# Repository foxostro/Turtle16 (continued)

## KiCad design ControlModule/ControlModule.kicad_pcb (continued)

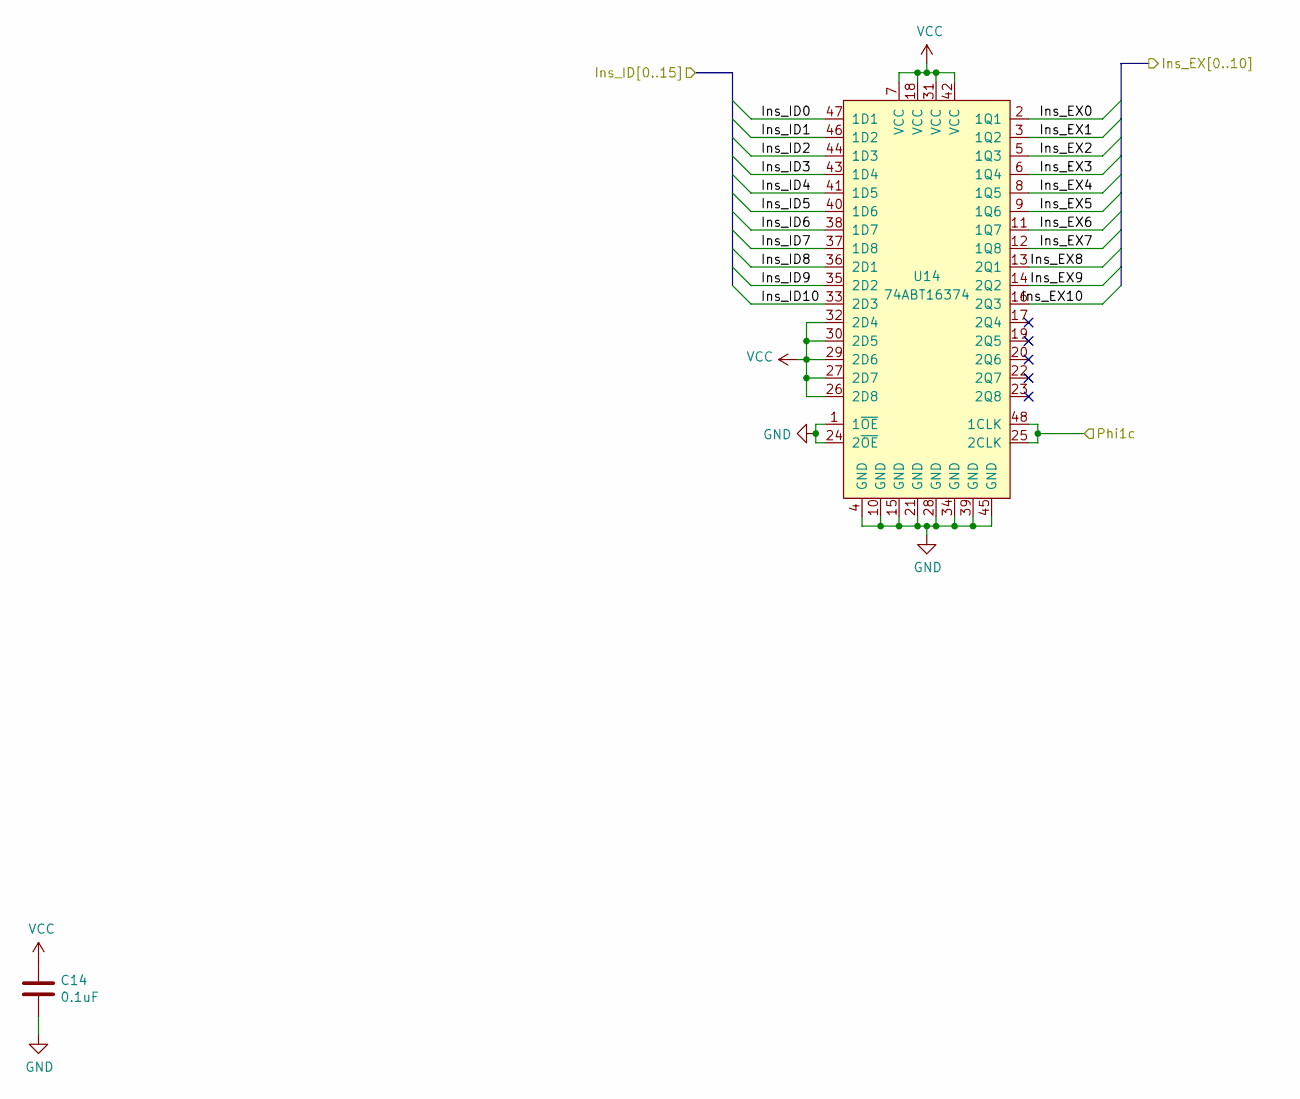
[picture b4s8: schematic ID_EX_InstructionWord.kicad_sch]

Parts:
C14: 0.1uF; C_0603_1608Metric_Pad1.08x0.95mm_HandSolder
U14: 74ABT16374; TSSOP-48_6.1x12.5mm_P0.5mm

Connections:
/ID Prototype Inputs/Ins_ID0: U14.47 (1D1); also elsewhere on the board
/ID Prototype Inputs/Ins_ID1: U14.46 (1D2); also elsewhere on the board
/ID Prototype Inputs/Ins_ID2: U14.44 (1D3); also elsewhere on the board
/ID Prototype Inputs/Ins_ID3: U14.43 (1D4); also elsewhere on the board
/ID Prototype Inputs/Ins_ID4: U14.41 (1D5); also elsewhere on the board
/ID Prototype Inputs/Ins_ID5: U14.40 (1D6); also elsewhere on the board
/ID Prototype Inputs/Ins_ID6: U14.38 (1D7); also elsewhere on the board
/ID Prototype Inputs/Ins_ID7: U14.37 (1D8); also elsewhere on the board
/ID Prototype Inputs/Ins_ID8: U14.36 (2D1); also elsewhere on the board
/ID Prototype Inputs/Ins_ID9: U14.35 (2D2); also elsewhere on the board
/ID Prototype Inputs/Ins_ID10: U14.33 (2D3); also elsewhere on the board
/ID Prototype Inputs/Phi1c: U14.25 (2CLK), U14.48 (1CLK); also elsewhere on the board
/ID Prototype Outputs/Ins_EX0: U14.2 (1Q1); also elsewhere on the board
/ID Prototype Outputs/Ins_EX1: U14.3 (1Q2); also elsewhere on the board
/ID Prototype Outputs/Ins_EX2: U14.5 (1Q3); also elsewhere on the board
/ID Prototype Outputs/Ins_EX3: U14.6 (1Q4); also elsewhere on the board
/ID Prototype Outputs/Ins_EX4: U14.8 (1Q5); also elsewhere on the board
/ID Prototype Outputs/Ins_EX5: U14.9 (1Q6); also elsewhere on the board
/ID Prototype Outputs/Ins_EX6: U14.11 (1Q7); also elsewhere on the board
/ID Prototype Outputs/Ins_EX7: U14.12 (1Q8); also elsewhere on the board
/ID Prototype Outputs/Ins_EX8: U14.13 (2Q1); also elsewhere on the board
/ID Prototype Outputs/Ins_EX9: U14.14 (2Q2); also elsewhere on the board
/ID Prototype Outputs/Ins_EX10: U14.16 (2Q3); also elsewhere on the board
GND: C14.2, U14.1 (1~OE), U14.4 (GND), U14.10 (GND), U14.15 (GND), U14.21 (GND), U14.24 (2~OE), U14.28 (GND), U14.34 (GND), U14.39 (GND), U14.45 (GND); also elsewhere on the board
VCC: C14.1, U14.7 (VCC), U14.18 (VCC), U14.26 (2D8), U14.27 (2D7), U14.29 (2D6), U14.30 (2D5), U14.31 (VCC), U14.32 (2D4), U14.42 (VCC); also elsewhere on the board

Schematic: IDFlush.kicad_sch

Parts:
C2, C3, C4, C17: 0.1uF; C_0603_1608Metric_Pad1.08x0.95mm_HandSolder
U1, U18: 74HC245; TSSOP-20_4.4x6.5mm_P0.65mm
U2, U17: 74AHCT16245; TSSOP-48_6.1x12.5mm_P0.5mm

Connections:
/ID/Ctl_Mid0: U17.47 (1A1); also elsewhere on the board
/ID/Ctl_Mid1: U17.46 (1A2); also elsewhere on the board
/ID/Ctl_Mid2: U17.44 (1A3); also elsewhere on the board
/ID/Ctl_Mid3: U17.43 (1A4); also elsewhere on the board
/ID/Ctl_Mid4: U17.41 (1A5); also elsewhere on the board
/ID/Ctl_Mid5: U17.40 (1A6); also elsewhere on the board
/ID/Ctl_Mid6: U17.38 (1A7); also elsewhere on the board
/ID/Ctl_Mid7: U17.37 (1A8); also elsewhere on the board
/ID/Ctl_Mid8: U17.36 (2A1); also elsewhere on the board
/ID/Ctl_Mid9: U17.35 (2A2); also elsewhere on the board
/ID/Ctl_Mid10: U17.33 (2A3); also elsewhere on the board
/ID/Ctl_Mid11: U17.32 (2A4); also elsewhere on the board
/ID/Ctl_Mid12: U17.30 (2A5); also elsewhere on the board
/ID/Ctl_Mid13: U17.29 (2A6); also elsewhere on the board
/ID/Ctl_Mid14: U17.27 (2A7); also elsewhere on the board
/ID/Ctl_Mid15: U17.26 (2A8); also elsewhere on the board
/ID/Ctl_Mid16: U18.11 (B7); also elsewhere on the board
/ID/Ctl_Mid17: U18.12 (B6); also elsewhere on the board
/ID/Ctl_Mid18: U18.13 (B5); also elsewhere on the board
/ID/Ctl_Mid19: U18.14 (B4); also elsewhere on the board
/ID/Ctl_Mid20: U18.15 (B3); also elsewhere on the board
/ID/Ctl_Mid21: U18.16 (B2); also elsewhere on the board
/ID/Ctl_Mid22: U18.17 (B1); also elsewhere on the board
/ID/Ctl_Mid23: U18.18 (B0); also elsewhere on the board
/ID/Hazard Control/FLUSH: U17.25 (2~OE), U17.48 (1~OE), U18.19 (CE); also elsewhere on the board
/ID/Hazard Control/~FLUSH: U1.19 (CE), U2.25 (2~OE), U2.48 (1~OE); also elsewhere on the board
/ID/ID Flush/Ctl_ID0: U2.47 (1A1), U17.2 (1B1); also elsewhere on the board
/ID/ID Flush/Ctl_ID1: U2.46 (1A2), U17.3 (1B2); also elsewhere on the board
/ID/ID Flush/Ctl_ID2: U2.44 (1A3), U17.5 (1B3); also elsewhere on the board
/ID/ID Flush/Ctl_ID3: U2.43 (1A4), U17.6 (1B4); also elsewhere on the board
/ID/ID Flush/Ctl_ID4: U2.41 (1A5), U17.8 (1B5); also elsewhere on the board
/ID/ID Flush/Ctl_ID5: U2.40 (1A6), U17.9 (1B6); also elsewhere on the board
/ID/ID Flush/Ctl_ID6: U2.38 (1A7), U17.11 (1B7); also elsewhere on the board
/ID/ID Flush/Ctl_ID7: U2.37 (1A8), U17.12 (1B8); also elsewhere on the board
/ID/ID Flush/Ctl_ID8: U2.36 (2A1), U17.13 (2B1); also elsewhere on the board
/ID/ID Flush/Ctl_ID9: U2.35 (2A2), U17.14 (2B2); also elsewhere on the board
/ID/ID Flush/Ctl_ID10: U2.33 (2A3), U17.16 (2B3); also elsewhere on the board
/ID/ID Flush/Ctl_ID11: U2.32 (2A4), U17.17 (2B4); also elsewhere on the board
/ID/ID Flush/Ctl_ID12: U2.30 (2A5), U17.19 (2B5); also elsewhere on the board
/ID/ID Flush/Ctl_ID13: U2.29 (2A6), U17.20 (2B6); also elsewhere on the board
/ID/ID Flush/Ctl_ID14: U2.27 (2A7), U17.22 (2B7); also elsewhere on the board
/ID/ID Flush/Ctl_ID15: U2.26 (2A8), U17.23 (2B8); also elsewhere on the board
/ID/ID Flush/Ctl_ID16: U1.11 (B7), U18.9 (A7); also elsewhere on the board
/ID/ID Flush/Ctl_ID17: U1.12 (B6), U18.8 (A6); also elsewhere on the board
/ID/ID Flush/Ctl_ID18: U1.13 (B5), U18.7 (A5); also elsewhere on the board
/ID/ID Flush/Ctl_ID19: U1.14 (B4), U18.6 (A4); also elsewhere on the board
/ID/ID Flush/Ctl_ID20: U1.15 (B3), U18.5 (A3); also elsewhere on the board
/ID/ID Flush/Ctl_ID21: U1.16 (B2), U18.4 (A2); also elsewhere on the board
/ID/ID Flush/Ctl_ID22: U1.17 (B1), U18.3 (A1); also elsewhere on the board
/ID/ID Flush/Ctl_ID23: U1.18 (B0), U18.2 (A0); also elsewhere on the board
GND: C2.2, C3.2, C4.2, C17.2, U1.10 (GND), U2.1 (1DIR), U2.4 (GND), U2.10 (GND), U2.15 (GND), U2.21 (GND), U2.24 (2DIR), U2.28 (GND), U2.34 (GND), U2.39 (GND), U2.45 (GND), U17.4 (GND), U17.10 (GND), U17.15 (GND), U17.21 (GND), U17.28 (GND), U17.34 (GND), U17.39 (GND), U17.45 (GND), U18.1 (A->B), U18.10 (GND); also elsewhere on the board
VCC: C2.1, C3.1, C4.1, C17.1, U1.1 (A->B), U1.2 (A0), U1.3 (A1), U1.4 (A2), U1.5 (A3), U1.6 (A4), U1.7 (A5), U1.8 (A6), U1.9 (A7), U1.20 (VCC), U2.2 (1B1), U2.3 (1B2), U2.5 (1B3), U2.6 (1B4), U2.7 (VCC), U2.8 (1B5), U2.9 (1B6), U2.11 (1B7), U2.12 (1B8), U2.13 (2B1), U2.14 (2B2), U2.16 (2B3), U2.17 (2B4), U2.18 (VCC), U2.19 (2B5), U2.20 (2B6), U2.22 (2B7), U2.23 (2B8), U2.31 (VCC), U2.42 (VCC), U17.1 (1DIR), U17.7 (VCC), U17.18 (VCC), U17.24 (2DIR), U17.31 (VCC), U17.42 (VCC), U18.20 (VCC); also elsewhere on the board

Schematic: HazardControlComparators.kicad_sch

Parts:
C10, C11, C12, C13: 0.1uF; C_0603_1608Metric_Pad1.08x0.95mm_HandSolder
TP34: SEL_B_MATCHES_SEL_C_MEM; TestPoint_Pad_D1.0mm
TP35: SEL_A_MATCHES_SEL_C_MEM; TestPoint_Pad_D1.0mm
TP36: SEL_A_MATCHES_SEL_C_EX; TestPoint_Pad_D1.0mm
TP37: SEL_B_MATCHES_SEL_C_EX; TestPoint_Pad_D1.0mm
U10, U11, U12, U13: 74F521; SOIC-20W_7.5x12.8mm_P1.27mm

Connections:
/ID Prototype Inputs/Ins_ID2: U11.2 (P0), U12.2 (P0); also elsewhere on the board
/ID Prototype Inputs/Ins_ID3: U11.4 (P1), U12.4 (P1); also elsewhere on the board
/ID Prototype Inputs/Ins_ID4: U11.6 (P2), U12.6 (P2); also elsewhere on the board
/ID Prototype Inputs/Ins_ID5: U10.2 (P0), U13.2 (P0); also elsewhere on the board
/ID Prototype Inputs/Ins_ID6: U10.4 (P1), U13.4 (P1); also elsewhere on the board
/ID Prototype Inputs/Ins_ID7: U10.6 (P2), U13.6 (P2); also elsewhere on the board
/ID Prototype Inputs/SelC_MEM0: U12.3 (Q0), U13.3 (Q0); also elsewhere on the board
/ID Prototype Inputs/SelC_MEM1: U12.5 (Q1), U13.5 (Q1); also elsewhere on the board
/ID Prototype Inputs/SelC_MEM2: U12.7 (Q2), U13.7 (Q2); also elsewhere on the board
/ID Prototype Outputs/Ins_EX8: U10.3 (Q0), U11.3 (Q0); also elsewhere on the board
/ID Prototype Outputs/Ins_EX9: U10.5 (Q1), U11.5 (Q1); also elsewhere on the board
/ID Prototype Outputs/Ins_EX10: U10.7 (Q2), U11.7 (Q2); also elsewhere on the board
/ID/Hazard Control/Hazard Control Comparators/SEL_A_MATCHES_SEL_C_EX: TP36.1, U10.19 (~P=Q); also elsewhere on the board
/ID/Hazard Control/Hazard Control Comparators/SEL_A_MATCHES_SEL_C_MEM: TP35.1, U13.19 (~P=Q); also elsewhere on the board
/ID/Hazard Control/Hazard Control Comparators/SEL_B_MATCHES_SEL_C_EX: TP37.1, U11.19 (~P=Q); also elsewhere on the board
/ID/Hazard Control/Hazard Control Comparators/SEL_B_MATCHES_SEL_C_MEM: TP34.1, U12.19 (~P=Q); also elsewhere on the board
GND: C10.2, C11.2, C12.2, C13.2, U10.1 (~OE), U10.8 (P3), U10.9 (Q3), U10.10 (GND), U10.11 (P4), U10.12 (Q4), U10.13 (P5), U10.14 (Q5), U10.15 (P6), U10.16 (Q6), U10.17 (P7), U10.18 (Q7), U11.1 (~OE), U11.8 (P3), U11.9 (Q3), U11.10 (GND), U11.11 (P4), U11.12 (Q4), U11.13 (P5), U11.14 (Q5), U11.15 (P6), U11.16 (Q6), U11.17 (P7), U11.18 (Q7), U12.1 (~OE), U12.8 (P3), U12.9 (Q3), U12.10 (GND), U12.11 (P4), U12.12 (Q4), U12.13 (P5), U12.14 (Q5), U12.15 (P6), U12.16 (Q6), U12.17 (P7), U12.18 (Q7), U13.1 (~OE), U13.8 (P3), U13.9 (Q3), U13.10 (GND), U13.11 (P4), U13.12 (Q4), U13.13 (P5), U13.14 (Q5), U13.15 (P6), U13.16 (Q6), U13.17 (P7), U13.18 (Q7); also elsewhere on the board
VCC: C10.1, C11.1, C12.1, C13.1, U10.20 (VCC), U11.20 (VCC), U12.20 (VCC), U13.20 (VCC); also elsewhere on the board

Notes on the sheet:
SelA0
SelB1
SelA2
SelA1
SelB2
SelB0

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
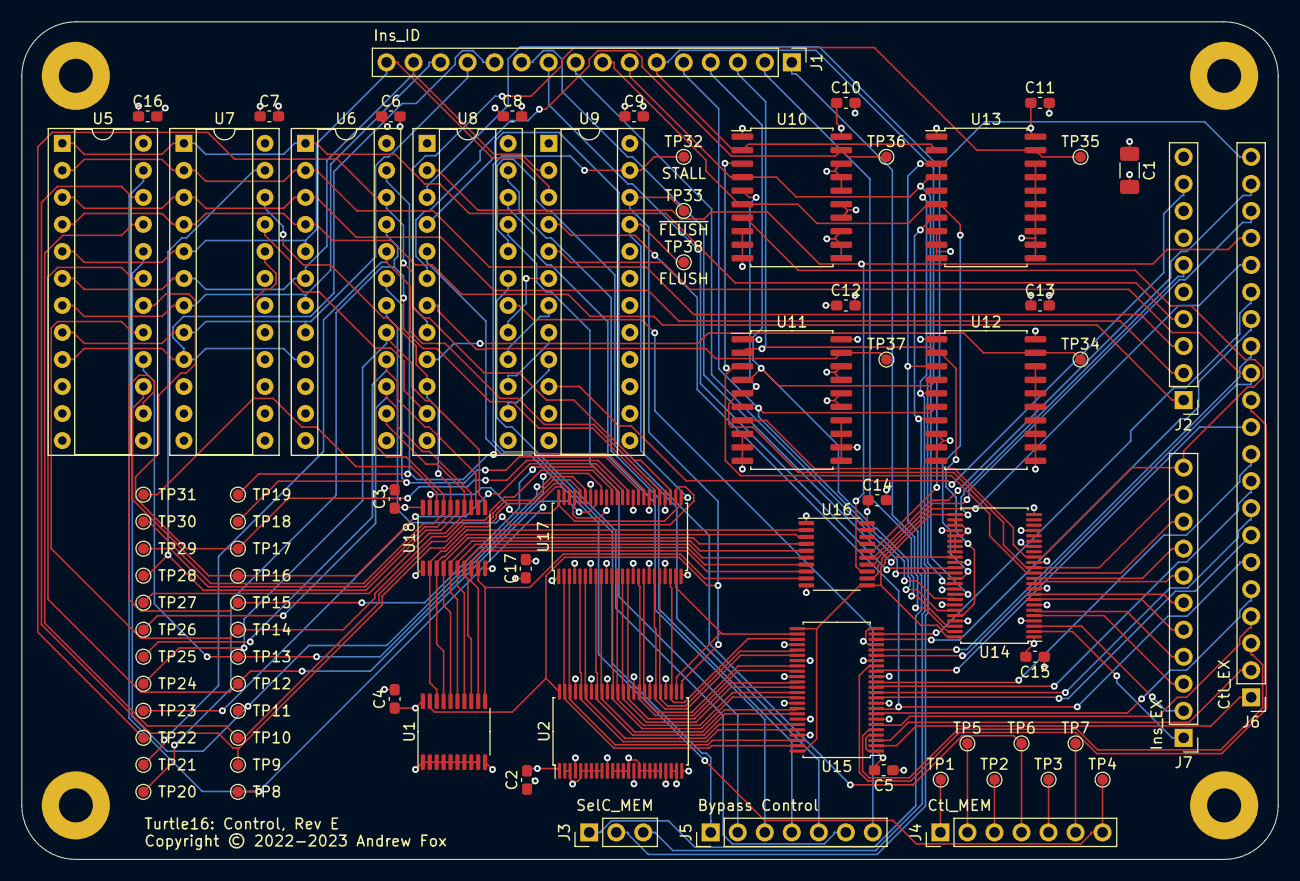
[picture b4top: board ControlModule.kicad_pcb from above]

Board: 4 copper layers, 118.1 x 78.7 mm, 82 parts (0 on the bottom side), 131 nets.

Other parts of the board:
TP2: Ctl_MEM16; TestPoint_Pad_D1.0mm
TP3: Ctl_Mid0; TestPoint_Pad_D1.0mm
TP4: Ctl_MEM20; TestPoint_Pad_D1.0mm
TP5: Ctl_MEM15; TestPoint_Pad_D1.0mm
TP6: Ctl_MEM17; TestPoint_Pad_D1.0mm
TP7: Ctl_MEM19; TestPoint_Pad_D1.0mm

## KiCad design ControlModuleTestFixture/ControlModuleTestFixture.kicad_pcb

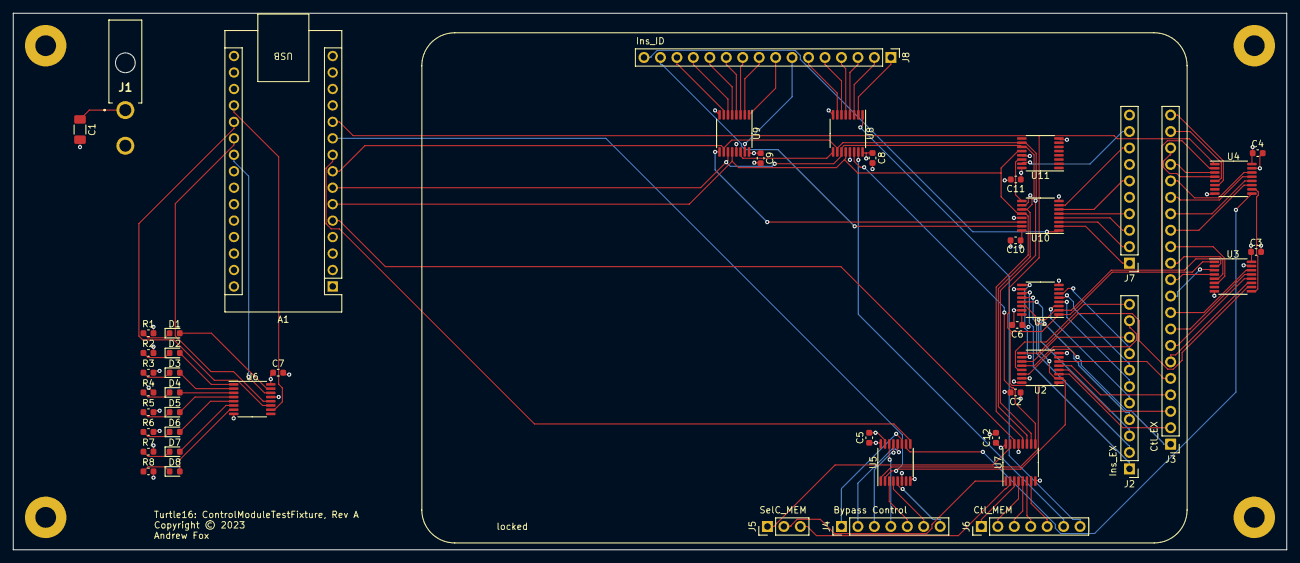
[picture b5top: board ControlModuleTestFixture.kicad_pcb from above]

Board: 4 copper layers, 196.5 x 82.8 mm, 52 parts (0 on the bottom side), 109 nets.

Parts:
A1: Arduino_Nano_Every; Arduino_Nano
C1: 100µF; C_1206_3216Metric_Pad1.33x1.80mm_HandSolder
C2, C3, C4, C5, C6, C7, C8, C9, C10, C11, C12: 0.1µF; C_0603_1608Metric
D1, D2, D3, D4, D5, D6, D7, D8: Red; LED_0603_1608Metric
H1, H2, H3, H4: MountingHole_Pad; MountingHole_3.2mm_M3_Pad
J1: Power; 172448-0002
J2: Ins_EX; PinHeader_1x11_P2.54mm_Vertical
J3: Ctl_EX; PinHeader_1x21_P2.54mm_Vertical
J4: Bypass Control; PinHeader_1x07_P2.54mm_Vertical
J5: SelC_MEM; PinHeader_1x03_P2.54mm_Vertical
J6: Ctl_MEM; PinHeader_1x07_P2.54mm_Vertical
J7: Control Signals; PinHeader_1x10_P2.54mm_Vertical
J8: Ins_ID; PinHeader_1x16_P2.54mm_Vertical
R1, R2, R3, R4, R5, R6, R7, R8: 270R; C_0603_1608Metric
U1, U2, U3, U4, U5: 74HC165; TSSOP-16_4.4x5mm_P0.65mm
U6, U7, U8, U9, U10, U11: 74HC595; TSSOP-16_4.4x5mm_P0.65mm

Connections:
/ID Prototype Inputs/Carry: J7.1, U10.2 (QC)
/ID Prototype Inputs/Ctl_MEM14: J6.1, U7.3 (QD)
/ID Prototype Inputs/Ctl_MEM15: J6.2, U7.4 (QE)
/ID Prototype Inputs/Ctl_MEM16: J6.3, U7.5 (QF)
/ID Prototype Inputs/Ctl_MEM17: J6.4, U7.6 (QG)
/ID Prototype Inputs/Ctl_MEM18: J6.5, U7.7 (QH)
/ID Prototype Inputs/Ctl_MEM19: J6.6, U8.15 (QA)
/ID Prototype Inputs/Ctl_MEM20: J6.7, U8.1 (QB)
/ID Prototype Inputs/Ins_ID0: J8.1, U8.2 (QC)
/ID Prototype Inputs/Ins_ID1: J8.2, U8.3 (QD)
/ID Prototype Inputs/Ins_ID2: J8.3, U8.4 (QE)
/ID Prototype Inputs/Ins_ID3: J8.4, U8.5 (QF)
/ID Prototype Inputs/Ins_ID4: J8.5, U8.6 (QG)
/ID Prototype Inputs/Ins_ID5: J8.6, U8.7 (QH)
/ID Prototype Inputs/Ins_ID6: J8.7, U9.15 (QA)
/ID Prototype Inputs/Ins_ID7: J8.8, U9.1 (QB)
/ID Prototype Inputs/Ins_ID8: J8.9, U9.2 (QC)
/ID Prototype Inputs/Ins_ID9: J8.10, U9.3 (QD)
/ID Prototype Inputs/Ins_ID10: J8.11, U9.4 (QE)
/ID Prototype Inputs/Ins_ID11: J8.12, U9.5 (QF)
/ID Prototype Inputs/Ins_ID12: J8.13, U9.6 (QG)
/ID Prototype Inputs/Ins_ID13: J8.14, U9.7 (QH)
/ID Prototype Inputs/Ins_ID14: J8.15, U10.15 (QA)
/ID Prototype Inputs/Ins_ID15: J8.16, U10.1 (QB)
/ID Prototype Inputs/N: J7.4, U10.5 (QF)
/ID Prototype Inputs/OVF: J7.3, U10.4 (QE)
/ID Prototype Inputs/Phi1c: J7.6, U10.6 (QG)
/ID Prototype Inputs/Phi2: J7.8, U10.7 (QH)
/ID Prototype Inputs/SelC_MEM0: J5.1, U7.15 (QA)
/ID Prototype Inputs/SelC_MEM1: J5.2, U7.1 (QB)
/ID Prototype Inputs/SelC_MEM2: J5.3, U7.2 (QC)
/ID Prototype Inputs/Z: J7.2, U10.3 (QD)
/ID Prototype Inputs/~RST_sync: J7.9, U11.15 (QA)
/ID Prototype Outputs/Ctl_EX0: J3.1, U2.14 (D3)
/ID Prototype Outputs/Ctl_EX1: J3.2, U2.3 (D4)
/ID Prototype Outputs/Ctl_EX2: J3.3, U2.4 (D5)
/ID Prototype Outputs/Ctl_EX3: J3.4, U2.5 (D6)
/ID Prototype Outputs/Ctl_EX4: J3.5, U2.6 (D7)
/ID Prototype Outputs/Ctl_EX5: J3.6, U3.11 (D0)
/ID Prototype Outputs/Ctl_EX6: J3.7, U3.12 (D1)
/ID Prototype Outputs/Ctl_EX7: J3.8, U3.13 (D2)
/ID Prototype Outputs/Ctl_EX8: J3.9, U3.14 (D3)
/ID Prototype Outputs/Ctl_EX9: J3.10, U3.3 (D4)
/ID Prototype Outputs/Ctl_EX10: J3.11, U3.4 (D5)
/ID Prototype Outputs/Ctl_EX11: J3.12, U3.5 (D6)
/ID Prototype Outputs/Ctl_EX12: J3.13, U3.6 (D7)
/ID Prototype Outputs/Ctl_EX13: J3.14, U4.11 (D0)
/ID Prototype Outputs/Ctl_EX14: J3.15, U4.12 (D1)
/ID Prototype Outputs/Ctl_EX15: J3.16, U4.13 (D2)
/ID Prototype Outputs/Ctl_EX16: J3.17, U4.14 (D3)
/ID Prototype Outputs/Ctl_EX17: J3.18, U4.3 (D4)
/ID Prototype Outputs/Ctl_EX18: J3.19, U4.4 (D5)
/ID Prototype Outputs/Ctl_EX19: J3.20, U4.5 (D6)
/ID Prototype Outputs/Ctl_EX20: J3.21, U4.6 (D7)
/ID Prototype Outputs/FWD_A: J4.2, U5.12 (D1)
/ID Prototype Outputs/FWD_B: J4.5, U5.3 (D4)
/ID Prototype Outputs/FWD_EX_TO_A: J4.3, U5.13 (D2)
/ID Prototype Outputs/FWD_EX_TO_B: J4.6, U5.4 (D5)
/ID Prototype Outputs/FWD_MEM_TO_A: J4.4, U5.14 (D3)
/ID Prototype Outputs/FWD_MEM_TO_B: J4.7, U5.5 (D6)
/ID Prototype Outputs/Ins_EX0: J2.1, U1.11 (D0)
/ID Prototype Outputs/Ins_EX1: J2.2, U1.12 (D1)
/ID Prototype Outputs/Ins_EX2: J2.3, U1.13 (D2)
/ID Prototype Outputs/Ins_EX3: J2.4, U1.14 (D3)
/ID Prototype Outputs/Ins_EX4: J2.5, U1.3 (D4)
/ID Prototype Outputs/Ins_EX5: J2.6, U1.4 (D5)
/ID Prototype Outputs/Ins_EX6: J2.7, U1.5 (D6)
/ID Prototype Outputs/Ins_EX7: J2.8, U1.6 (D7)
/ID Prototype Outputs/Ins_EX8: J2.9, U2.11 (D0)
/ID Prototype Outputs/Ins_EX9: J2.10, U2.12 (D1)
/ID Prototype Outputs/Ins_EX10: J2.11, U2.13 (D2)
/ID Prototype Outputs/STALL: J4.1, U5.11 (D0)
/LED Output/RCLK: A1.21 (A2), U6.12 (RCLK)
/LED Output/SCK: A1.20 (A1), U6.11 (SRCLK)
/LED Output/SI: A1.22 (A3), U6.14 (SER)
/LED Output/~CLR: A1.19 (A0), U6.10 (~SRCLR)
/Test Fixture Inputs/SCK: A1.10 (D7), U1.2 (CP), U2.2 (CP), U3.2 (CP), U4.2 (CP), U5.2 (CP)
/Test Fixture Inputs/SO: A1.9 (D6), U5.9 (Q7)
/Test Fixture Inputs/~PL: A1.11 (D8), U1.1 (~PL), U2.1 (~PL), U3.1 (~PL), U4.1 (~PL), U5.1 (~PL)
/Test Fixture Outputs/RCLK: A1.6 (D3), U7.12 (RCLK), U8.12 (RCLK), U9.12 (RCLK), U10.12 (RCLK), U11.12 (RCLK)
/Test Fixture Outputs/SCK: A1.7 (D4), U7.11 (SRCLK), U8.11 (SRCLK), U9.11 (SRCLK), U10.11 (SRCLK), U11.11 (SRCLK)
/Test Fixture Outputs/SI: A1.5 (D2), U7.14 (SER)
/Test Fixture Outputs/~CLR: A1.8 (D5), U7.10 (~SRCLR), U8.10 (~SRCLR), U9.10 (~SRCLR), U10.10 (~SRCLR), U11.10 (~SRCLR)
GND: A1.4 (GND), A1.29 (GND), C1.2, C2.2, C3.2, C4.2, C5.2, C6.2, C7.2, C8.2, C9.2, C10.2, C11.2, C12.2, H1.1, H2.1, H3.1, H4.1, J1.2, J7.5, J7.7, R1.2, R2.2, R3.2, R4.2, R5.2, R6.2, R7.2, R8.2, U1.8 (GND), U1.10 (DS), U1.15 (~CE), U2.8 (GND), U2.15 (~CE), U3.8 (GND), U3.15 (~CE), U4.8 (GND), U4.15 (~CE), U5.6 (D7), U5.8 (GND), U5.15 (~CE), U6.8 (GND), U6.13 (~OE), U7.8 (GND), U7.13 (~OE), U8.8 (GND), U8.13 (~OE), U9.8 (GND), U9.13 (~OE), U10.8 (GND), U10.13 (~OE), U11.8 (GND), U11.13 (~OE)
unnamed: D1.2 (A), U6.15 (QA)
unnamed: D1.1 (K), R1.1
unnamed: D2.2 (A), U6.1 (QB)
unnamed: D2.1 (K), R2.1
unnamed: D3.2 (A), U6.2 (QC)
unnamed: D3.1 (K), R3.1
unnamed: D4.2 (A), U6.3 (QD)
unnamed: D4.1 (K), R4.1
unnamed: D5.2 (A), U6.4 (QE)
unnamed: D5.1 (K), R5.1
unnamed: D6.2 (A), U6.5 (QF)
unnamed: D6.1 (K), R6.1
unnamed: D7.2 (A), U6.6 (QG)
unnamed: D7.1 (K), R7.1
unnamed: D8.2 (A), U6.7 (QH)
unnamed: D8.1 (K), R8.1
unnamed: U1.9 (Q7), U2.10 (DS)
unnamed: U2.9 (Q7), U3.10 (DS)
unnamed: U3.9 (Q7), U4.10 (DS)
unnamed: U4.9 (Q7), U5.10 (DS)
unnamed: U7.9 (QH'), U8.14 (SER)
unnamed: U8.9 (QH'), U9.14 (SER)
unnamed: U10.9 (QH'), U11.14 (SER)
unnamed: U9.9 (QH'), U10.14 (SER)
VCC: A1.3 (~RESET), A1.28 (~RESET), A1.30 (VIN), C1.1, C2.1, C3.1, C4.1, C5.1, C6.1, C7.1, C8.1, C9.1, C10.1, C11.1, C12.1, J1.1, J7.10, U1.16 (VCC), U2.16 (VCC), U3.16 (VCC), U4.16 (VCC), U5.16 (VCC), U6.16 (VCC), U7.16 (VCC), U8.16 (VCC), U9.16 (VCC), U10.16 (VCC), U11.16 (VCC)

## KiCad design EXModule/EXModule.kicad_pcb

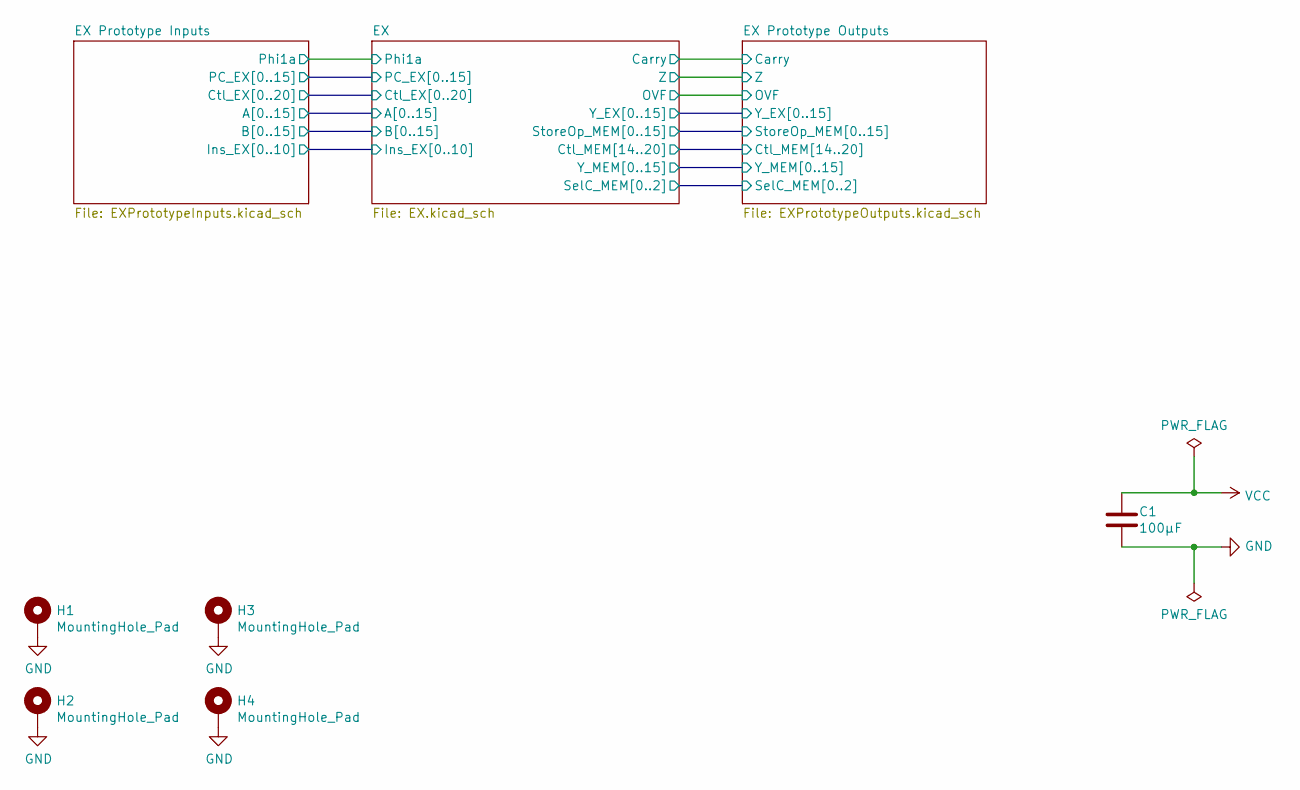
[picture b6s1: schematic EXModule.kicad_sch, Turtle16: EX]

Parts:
C1: 100µF; C_1206_3216Metric_Pad1.33x1.80mm_HandSolder
H1, H2, H3, H4: MountingHole_Pad; MountingHole_3.2mm_M3_Pad

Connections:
GND: C1.2, H1.1, H2.1, H3.1, H4.1; also elsewhere on the board
VCC: C1.1; also elsewhere on the board

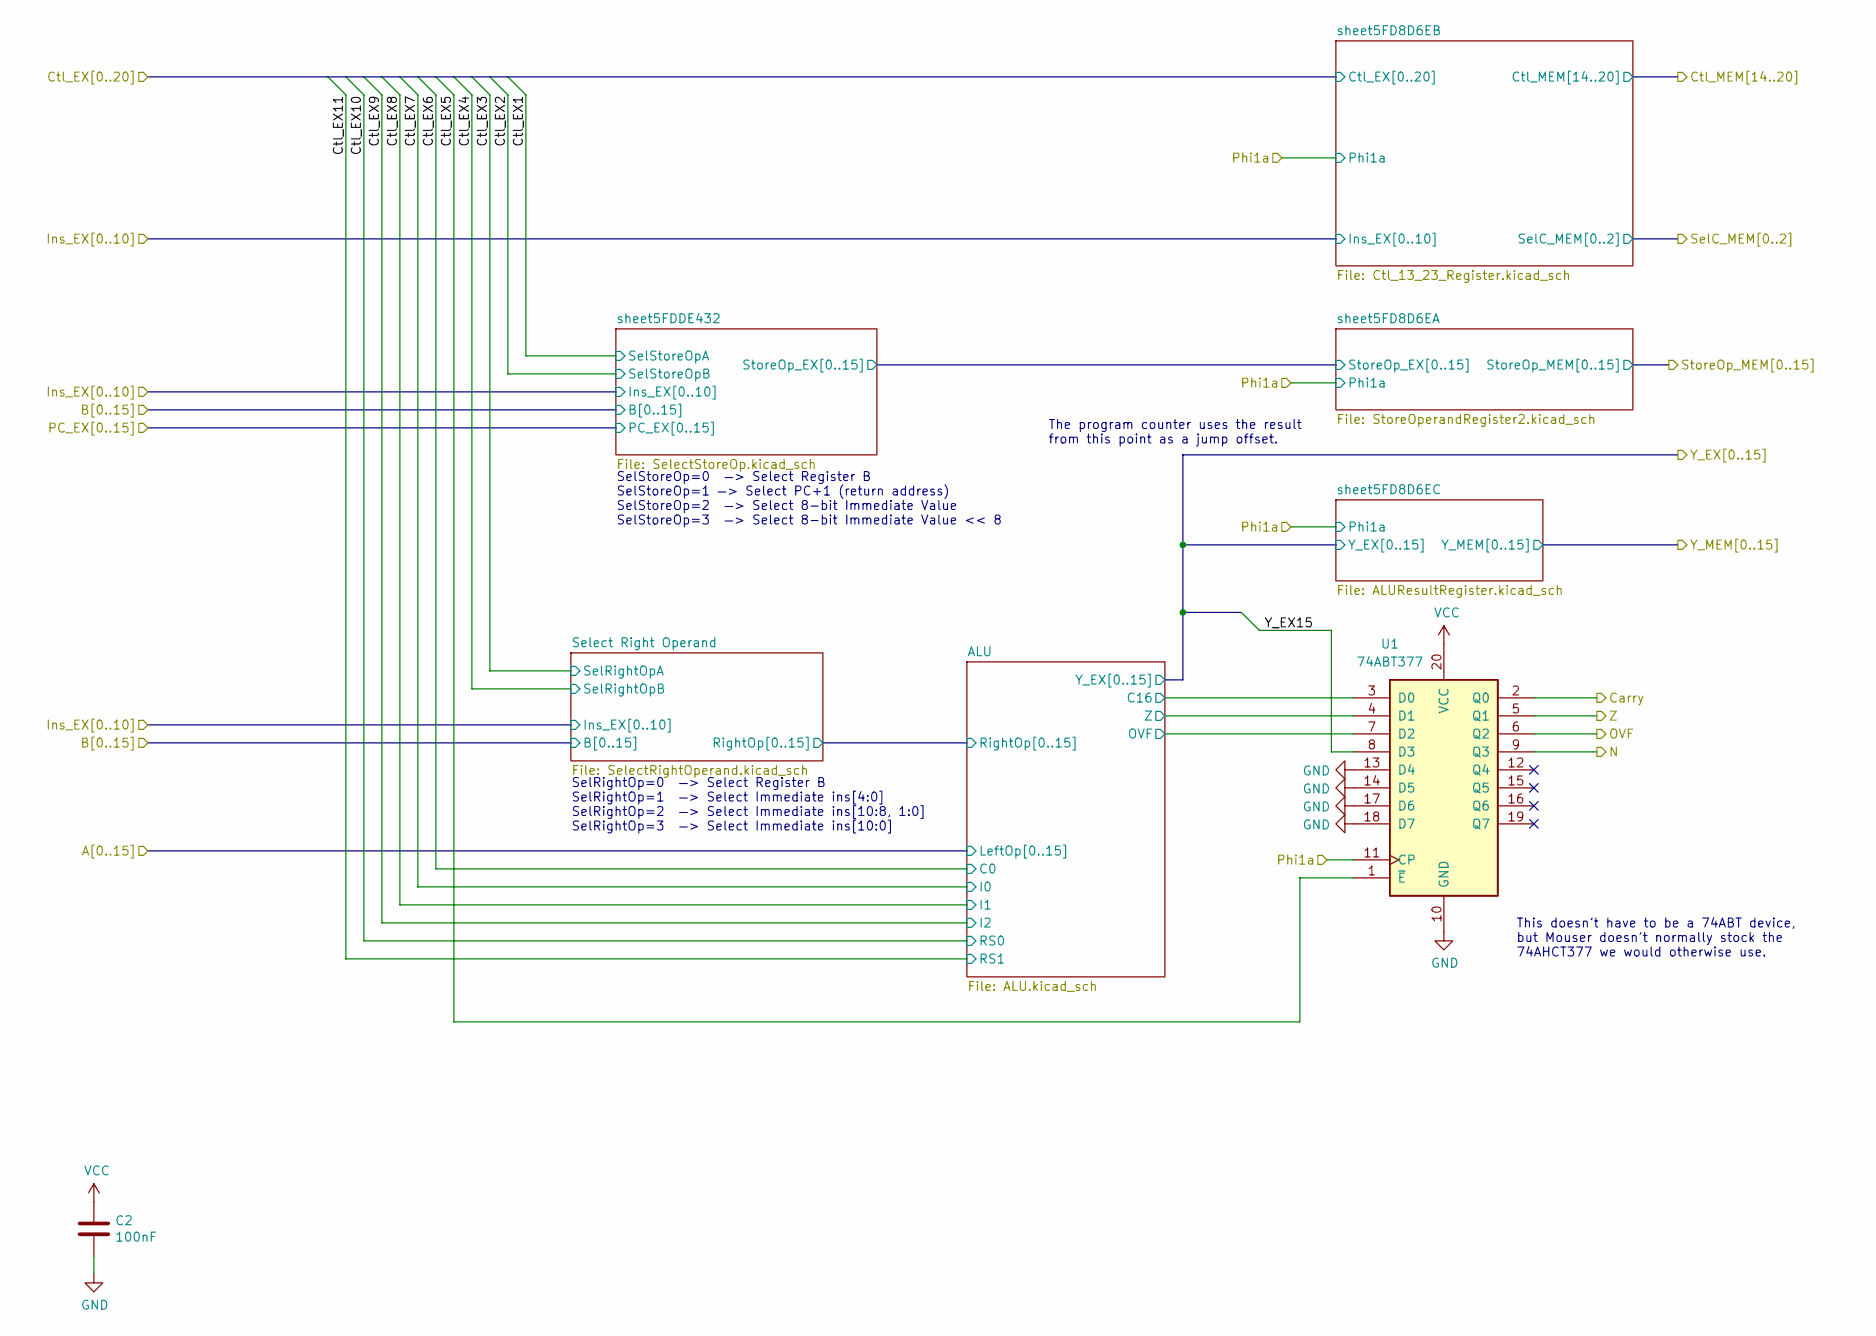
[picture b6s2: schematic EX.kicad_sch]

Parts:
C2: 100nF; C_0603_1608Metric_Pad1.08x0.95mm_HandSolder
U1: 74ABT377; TSSOP-20_4.4x6.5mm_P0.65mm

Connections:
/EX Prototype Inputs/Ctl_EX5: U1.1 (~E); also elsewhere on the board
/EX Prototype Inputs/Phi1a: U1.11 (CP); also elsewhere on the board
/EX Prototype Outputs/Carry: U1.2 (Q0); also elsewhere on the board
/EX Prototype Outputs/N: U1.9 (Q3); also elsewhere on the board
/EX Prototype Outputs/OVF: U1.6 (Q2); also elsewhere on the board
/EX Prototype Outputs/Y_EX15: U1.8 (D3); also elsewhere on the board
/EX Prototype Outputs/Z: U1.5 (Q1); also elsewhere on the board
/EX/ALU/C16: U1.3 (D0); also elsewhere on the board
/EX/ALU/OVF: U1.7 (D2); also elsewhere on the board
/EX/ALU/Z: U1.4 (D1); also elsewhere on the board
GND: C2.2, U1.10 (GND), U1.13 (D4), U1.14 (D5), U1.17 (D6), U1.18 (D7); also elsewhere on the board
VCC: C2.1, U1.20 (VCC); also elsewhere on the board

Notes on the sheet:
SelStoreOp=0 —> Select Register B SelStoreOp=1 —> Select PC+1 (return address) SelStoreOp=2 —> Select 8-bit Immediate Value SelStoreOp=3 —> Select 8-bit Immediate Value << 8
This doesn’t have to be a 74ABT device, but Mouser doesn’t normally stock the 74AHCT377 we would otherwise use.
SelRightOp=0 —> Select Register B SelRightOp=1 —> Select Immediate ins[4:0] SelRightOp=2 —> Select Immediate ins[10:8, 1:0] SelRightOp=3 —> Select Immediate ins[10:0]
The program counter uses the result from this point as a jump offset.

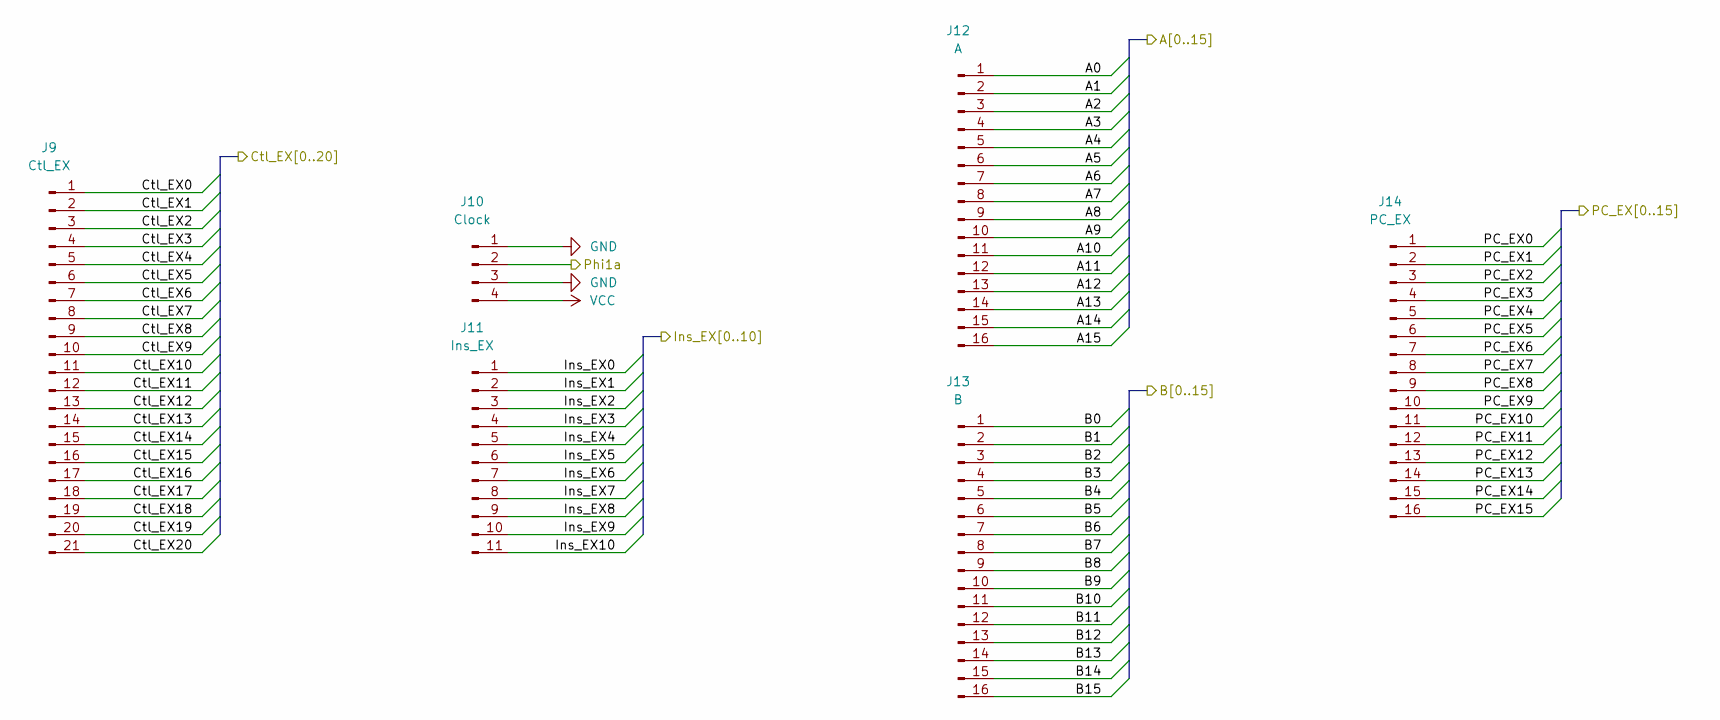
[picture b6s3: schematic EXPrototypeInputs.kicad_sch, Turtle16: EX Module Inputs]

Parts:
J9: Ctl_EX; PinHeader_1x21_P2.54mm_Vertical
J10: Clock; PinHeader_1x04_P2.54mm_Vertical
J11: Ins_EX; PinHeader_1x11_P2.54mm_Vertical
J12: A; PinHeader_1x16_P2.54mm_Vertical
J13: B; PinHeader_1x16_P2.54mm_Vertical
J14: PC_EX; PinHeader_1x16_P2.54mm_Vertical

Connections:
/EX Prototype Inputs/A0: J12.1; also elsewhere on the board
/EX Prototype Inputs/A1: J12.2; also elsewhere on the board
/EX Prototype Inputs/A2: J12.3; also elsewhere on the board
/EX Prototype Inputs/A3: J12.4; also elsewhere on the board
/EX Prototype Inputs/A4: J12.5; also elsewhere on the board
/EX Prototype Inputs/A5: J12.6; also elsewhere on the board
/EX Prototype Inputs/A6: J12.7; also elsewhere on the board
/EX Prototype Inputs/A7: J12.8; also elsewhere on the board
/EX Prototype Inputs/A8: J12.9; also elsewhere on the board
/EX Prototype Inputs/A9: J12.10; also elsewhere on the board
/EX Prototype Inputs/A10: J12.11; also elsewhere on the board
/EX Prototype Inputs/A11: J12.12; also elsewhere on the board
/EX Prototype Inputs/A12: J12.13; also elsewhere on the board
/EX Prototype Inputs/A13: J12.14; also elsewhere on the board
/EX Prototype Inputs/A14: J12.15; also elsewhere on the board
/EX Prototype Inputs/A15: J12.16; also elsewhere on the board
/EX Prototype Inputs/B0: J13.1; also elsewhere on the board
/EX Prototype Inputs/B1: J13.2; also elsewhere on the board
/EX Prototype Inputs/B2: J13.3; also elsewhere on the board
/EX Prototype Inputs/B3: J13.4; also elsewhere on the board
/EX Prototype Inputs/B4: J13.5; also elsewhere on the board
/EX Prototype Inputs/B5: J13.6; also elsewhere on the board
/EX Prototype Inputs/B6: J13.7; also elsewhere on the board
/EX Prototype Inputs/B7: J13.8; also elsewhere on the board
/EX Prototype Inputs/B8: J13.9; also elsewhere on the board
/EX Prototype Inputs/B9: J13.10; also elsewhere on the board
/EX Prototype Inputs/B10: J13.11; also elsewhere on the board
/EX Prototype Inputs/B11: J13.12; also elsewhere on the board
/EX Prototype Inputs/B12: J13.13; also elsewhere on the board
/EX Prototype Inputs/B13: J13.14; also elsewhere on the board
/EX Prototype Inputs/B14: J13.15; also elsewhere on the board
/EX Prototype Inputs/B15: J13.16; also elsewhere on the board
/EX Prototype Inputs/Ctl_EX0: J9.1
/EX Prototype Inputs/Ctl_EX1: J9.2; also elsewhere on the board
/EX Prototype Inputs/Ctl_EX2: J9.3; also elsewhere on the board
/EX Prototype Inputs/Ctl_EX3: J9.4; also elsewhere on the board
/EX Prototype Inputs/Ctl_EX4: J9.5; also elsewhere on the board
/EX Prototype Inputs/Ctl_EX5: J9.6; also elsewhere on the board
/EX Prototype Inputs/Ctl_EX6: J9.7; also elsewhere on the board
/EX Prototype Inputs/Ctl_EX7: J9.8; also elsewhere on the board
/EX Prototype Inputs/Ctl_EX8: J9.9; also elsewhere on the board
/EX Prototype Inputs/Ctl_EX9: J9.10; also elsewhere on the board
/EX Prototype Inputs/Ctl_EX10: J9.11; also elsewhere on the board
/EX Prototype Inputs/Ctl_EX11: J9.12; also elsewhere on the board
/EX Prototype Inputs/Ctl_EX12: J9.13
/EX Prototype Inputs/Ctl_EX13: J9.14
/EX Prototype Inputs/Ctl_EX14: J9.15; also elsewhere on the board
/EX Prototype Inputs/Ctl_EX15: J9.16; also elsewhere on the board
/EX Prototype Inputs/Ctl_EX16: J9.17; also elsewhere on the board
/EX Prototype Inputs/Ctl_EX17: J9.18; also elsewhere on the board
/EX Prototype Inputs/Ctl_EX18: J9.19; also elsewhere on the board
/EX Prototype Inputs/Ctl_EX19: J9.20; also elsewhere on the board
/EX Prototype Inputs/Ctl_EX20: J9.21; also elsewhere on the board
/EX Prototype Inputs/Ins_EX0: J11.1; also elsewhere on the board
/EX Prototype Inputs/Ins_EX1: J11.2; also elsewhere on the board
/EX Prototype Inputs/Ins_EX2: J11.3; also elsewhere on the board
/EX Prototype Inputs/Ins_EX3: J11.4; also elsewhere on the board
/EX Prototype Inputs/Ins_EX4: J11.5; also elsewhere on the board
/EX Prototype Inputs/Ins_EX5: J11.6; also elsewhere on the board
/EX Prototype Inputs/Ins_EX6: J11.7; also elsewhere on the board
/EX Prototype Inputs/Ins_EX7: J11.8; also elsewhere on the board
/EX Prototype Inputs/Ins_EX8: J11.9; also elsewhere on the board
/EX Prototype Inputs/Ins_EX9: J11.10; also elsewhere on the board
/EX Prototype Inputs/Ins_EX10: J11.11; also elsewhere on the board
/EX Prototype Inputs/PC_EX0: J14.1; also elsewhere on the board
/EX Prototype Inputs/PC_EX1: J14.2; also elsewhere on the board
/EX Prototype Inputs/PC_EX2: J14.3; also elsewhere on the board
/EX Prototype Inputs/PC_EX3: J14.4; also elsewhere on the board
/EX Prototype Inputs/PC_EX4: J14.5; also elsewhere on the board
/EX Prototype Inputs/PC_EX5: J14.6; also elsewhere on the board
/EX Prototype Inputs/PC_EX6: J14.7; also elsewhere on the board
/EX Prototype Inputs/PC_EX7: J14.8; also elsewhere on the board
/EX Prototype Inputs/PC_EX8: J14.9; also elsewhere on the board
/EX Prototype Inputs/PC_EX9: J14.10; also elsewhere on the board
/EX Prototype Inputs/PC_EX10: J14.11; also elsewhere on the board
/EX Prototype Inputs/PC_EX11: J14.12; also elsewhere on the board
/EX Prototype Inputs/PC_EX12: J14.13; also elsewhere on the board
/EX Prototype Inputs/PC_EX13: J14.14; also elsewhere on the board
/EX Prototype Inputs/PC_EX14: J14.15; also elsewhere on the board
/EX Prototype Inputs/PC_EX15: J14.16; also elsewhere on the board
/EX Prototype Inputs/Phi1a: J10.2; also elsewhere on the board
GND: J10.1, J10.3; also elsewhere on the board
VCC: J10.4; also elsewhere on the board
